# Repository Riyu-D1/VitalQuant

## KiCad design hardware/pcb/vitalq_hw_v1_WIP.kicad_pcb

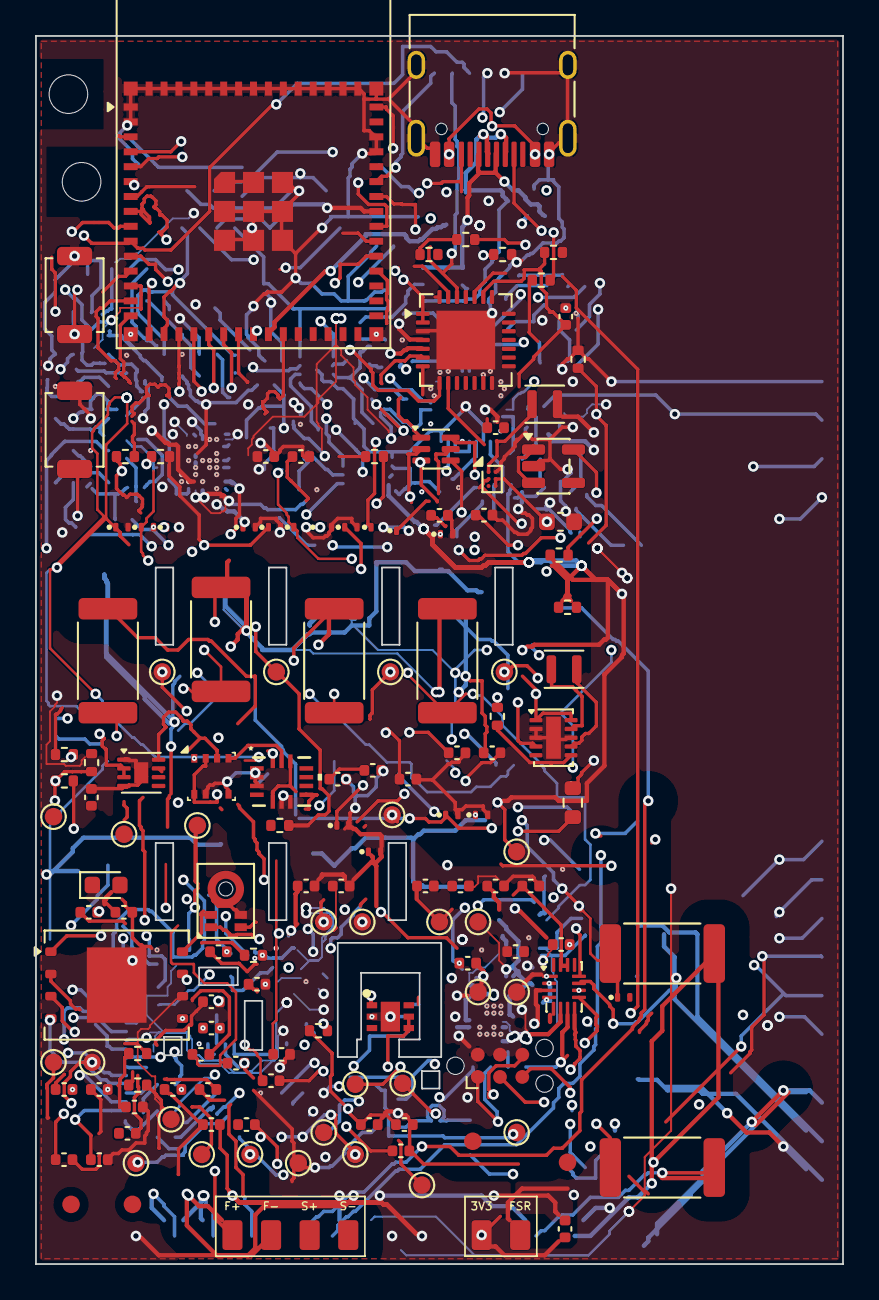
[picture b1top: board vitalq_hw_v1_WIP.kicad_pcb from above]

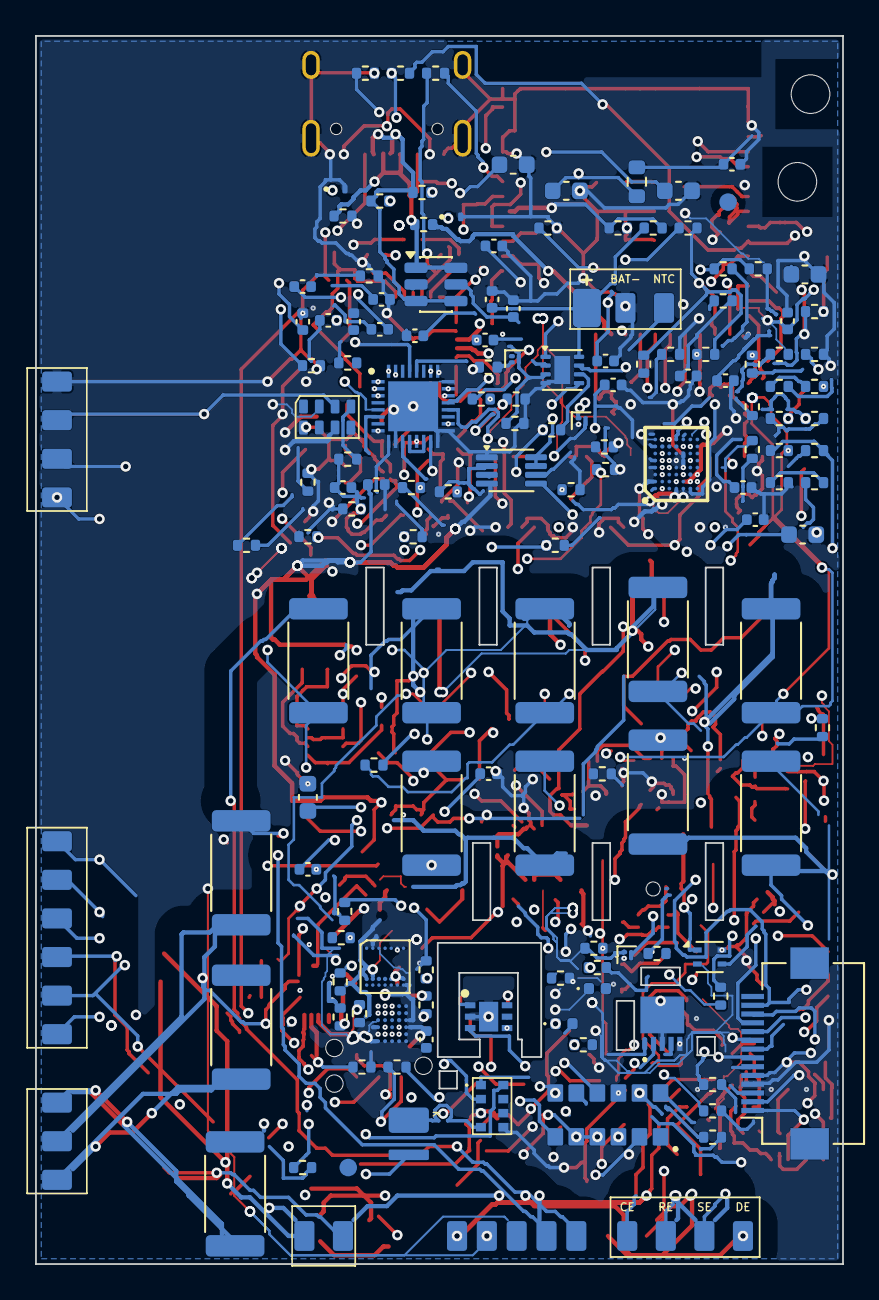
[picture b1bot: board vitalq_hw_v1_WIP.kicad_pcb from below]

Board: 6 copper layers, 46.0 x 70.0 mm, 292 parts (148 on the bottom side), 190 nets.

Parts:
C1, C47: 4.7u; C_0603_1608Metric
C2, C9, C20: 4.7u; C_0402_1005Metric
C3, C4, C6, C11, C14, C16, C19, C26, C32, C33, C42, C43, C64, C66, C80, C82, C83, C84: 1u; C_0402_1005Metric
C7, C45: 22u; C_0603_1608Metric
C8, C13, C15, C18, C24, C25, C27, C28, C29, C36, C37, C38, C39, C40, C41, C50, C51, C56, C57, C58, C59, C60, C61, C62, C63, C76, C77, C78, C79, C81: 100n; C_0402_1005Metric
C10: 1u; C_0603_1608Metric
C21, C22, C23, C55, C68, C69, C70: 470n; C_0402_1005Metric
C30: 10u; C_0402_1005Metric
C34: 47n; C_0402_1005Metric
C35: 4.7n; C_0402_1005Metric
C44: 10u; C_0603_1608Metric
C46: 2.2u; C_0402_1005Metric
C48, C49, C52, C53: 2.2n; C_0402_1005Metric
C54, C67: 15n; C_0402_1005Metric
C65: 1.5n; C_0402_1005Metric
C85: 47u; C_0603_1608Metric
D1, D2, D3, D4, D5, D6, D7, D8, D9, D21, D22, D23, D24, D26, D27, D28, D29, D30: TPD1E10B06; TPD1E10B06_DPY
D10: NF2W757G-F1; NF2W757G
D11: SFH4053; LED_0402_1005Metric
D12: SFH 4735 730nm; LED_0402_1005Metric
D25: KT-0603G; LED_0603_1608Metric
FID1, FID2, FID3, FID4, FID5, FID6: FID; Fiducial_1mm
H1, H2: M2; MountingHole_2.2mm_M2
J1: USB-C; USB_C_Receptacle_HRO_TYPE-C-31-M-12
J2: LiPo pads; Pads_LiPo
J3: FSR pads; Pads_FSR
J5: ECG pads; Pads_ECG
J6: EDA pads; Pads_EDA
J7: Chest bioZ; Pads_BIOZ
J8: TC2030; Tag-Connect_TC2030-IDC-NL_2x03_P1.27mm_Vertical
J9: I2C tail pads; Pads_1x04
J10: Optical tail pads; Pads_1x06
J11: Sweat site; Pads_1x03
J12: FH12-14S; Hirose_FH12-14S-0.5SH_1x14-1MP_P0.50mm_Horizontal
J13: MX ECG pads; Pads_1x02
L1: 0.47u; L_DFE201612E
L2: 1.0u; L_DFE201612E
Q1, Q2, Q4: CSD13380F3T; Texas_PicoStar_DFN-3_0.69x0.60mm
Q3: BC847BS,115; SOT-363_SC-70-6
R1, R2: 5.1k; R_0402_1005Metric
R3: 1.5k; R_0402_1005Metric
R5, R6, R7, R8, R9, R11, R14, R49, R52, R53, R60, R61, R65, R67, R68, R69, R70, R71, R74, R98, R100, R101, R112, R113, R115, R116, R117: 10k; R_0402_1005Metric
R10, R13, R39, R40, R41, R42, R62, R72, R73, R84, R85, R86, R87, R88: 1k; R_0402_1005Metric
R12: 10; R_0402_1005Metric
R15, R16, R17: 1M; R_0402_1005Metric
R18, R51: 200k; R_0402_1005Metric
R19, R20, R21, R22: 4.7k; R_0402_1005Metric
R23: 560k; R_0402_1005Metric
R24, R25, R44, R46, R48, R50, R59, R99, R107, R108, R110: 100k; R_0402_1005Metric
R26, R27, R28, R29: 10M; R_0402_1005Metric
R30, R31: 40.2k; R_0402_1005Metric
R32, R33, R34, R35, R36, R76, R77, R78, R79, R80, R81, R82, R83: 51k; R_2512_6332Metric
R43, R45: 5.11M; R_0402_1005Metric
R47, R109: 100; R_0402_1005Metric
R63: 22.1k; R_0402_1005Metric
R64: 47.5k; R_0402_1005Metric
R66: 301k; R_0402_1005Metric
R75: 27.0k; R_0402_1005Metric
R89, R90, R91, R92, R95, R96, R97, R102, R103, R104, R105, R106, R114: 0; R_0402_1005Metric
R93, R94: 0; R_0603_1608Metric
R118, R119, R120, R121, R122: 0; R_2512_6332Metric
SW1, SW2: TS-1088; SW_SPST_TS-1088-xR020
TP1: VBUS; TestPoint_Pad_D1.0mm
TP2: VBAT; TestPoint_Pad_D1.0mm
TP3: +3V3; TestPoint_Pad_D1.0mm
TP4: +1V8; TestPoint_Pad_D1.0mm
TP5: TX_5V; TestPoint_Pad_D1.0mm
TP6: VDD_CP2102; TestPoint_Pad_D1.0mm
TP7, TP8: GND; TestPoint_Pad_D1.0mm
TP9: ESP_EN; TestPoint_Pad_D1.0mm
TP10: ESP_IO0; TestPoint_Pad_D1.0mm
TP11: ESP_TX; TestPoint_Pad_D1.0mm
TP12: ESP_RX; TestPoint_Pad_D1.0mm
TP13: I2C_SDA; TestPoint_Pad_D1.0mm
TP14: I2C_SCL; TestPoint_Pad_D1.0mm
TP15: I2C_SDA_1V8; TestPoint_Pad_D1.0mm
TP16: I2C_SCL_1V8; TestPoint_Pad_D1.0mm
TP17: SPI_SCK; TestPoint_Pad_D1.0mm
TP18: SPI_MOSI; TestPoint_Pad_D1.0mm
TP19: SPI_MISO; TestPoint_Pad_D1.0mm
TP20: CS_ADS1292; TestPoint_Pad_D1.0mm
TP21: CS_AFE4900; TestPoint_Pad_D1.0mm
TP22: CS_AD5940; TestPoint_Pad_D1.0mm
TP23: CS_FLASH; TestPoint_Pad_D1.0mm
TP24: ADS1292_DRDY; TestPoint_Pad_D1.0mm
TP25: AFE4900_ADC_RDY; TestPoint_Pad_D1.0mm
TP26: EXP_INT; TestPoint_Pad_D1.0mm
TP27: CHG_STAT; TestPoint_Pad_D1.0mm
TP28: RTC_INT; TestPoint_Pad_D1.0mm
U1: ESP32-S3-MINI-1-N4R2; ESP32_S3_MINI_1
U2: BQ25170DSGR; Texas_DSG0008A_WSON-8-1EP_2x2mm_P0.5mm_EP0.9x1.6mm
U3: TPS63802DLAR; WSON-10-1EP_2x3mm_P0.5mm_EP0.84x2.4mm
U4: TPS7A2018PDBVR; SOT-23-5
U5: CP2102N-A02-GQFN28R; QFN-28-1EP_5x5mm_P0.5mm_EP3.35x3.35mm
U6: AFE4900YZR; BGA30N40P5X6_260X210X50
U7: AD5940BCBZ-RL7; BGA56C40P8X7_416X356X55
U8: ADS1292RIRSMT; QFN40P400X400X100-33N-D
U9: PCA9306DCUR; VSSOP-8_2.3x2mm_P0.5mm
U10: AS7341-DLGM; AS7341DLGT
U11, U20: TMP117AIDRVR; TMP117_DRV_NOPASTE
U12: MLX90632SLD-DCB-100-SP; MLX90632SLDDCB100SP
U13: BME280; Bosch_LGA-8_2.5x2.5mm_P0.65mm_ClockwisePinNumbering
U14: LSM6DSV80XTR; QFN_LSM6DSV80XTR_STM
U15: TPS61240YFFR; TPS61240_YFF
U16: SFH 7072; SFH7072
U17: MAX17048G+T10; TDFN-8-1EP_2x2mm_P0.5mm_EP0.8x1.2mm
U18: W25Q512JVEIQ; W25Q512_WSON8
U19: TCA6408ARSVR; TCA6408A_RSV
U21: USBLC6-2SC6; SOT-23-6
U22: MAX86178ENJ+; MAX86178_WLP49
U23: SHT45-AD1B; SHT45_DFN4
U24: RV-3028-C7; RV3028C7
U25: IM69D130

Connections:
+1V8: C36.1, R21.1, R22.1, R66.1, R97.2, TP4.1, U9.2, U10.1
+1V8_LDO: C6.1, R97.1, U4.5
+3V3: C4.1, C37.1, C38.1, C39.1, C40.1, C41.1, C45.1, C59.1, C60.1, C61.1, C76.1, C77.1, C78.1, C81.1, C84.1, D10.1, J3.1, J8.1, J9.1, J12.1, R5.1, R6.1, R7.1, R18.1, R19.1, R20.1, R23.1, R47.1, R49.1, R52.1, R53.1, R60.1, R65.1, R74.1, R94.1, R95.1, R98.1, R99.1, R109.1, R112.1, R113.1, R117.1, TP3.1, U3.6, U4.1, U4.3, U11.5, U12.2, U13.2, U13.6, U13.8, U14.5, U14.8, U14.12, U18.3, U18.7, U18.8, U19.14, U19.15, U20.4, U20.5, U22.F2, U23.3, U24.7, U25.2
+3V3_ANA: C11.1, C13.1, C16.1, C18.1, C28.1, C29.1, C43.1, C79.1, C80.1, R12.1, R15.1, R26.1, R28.1, R95.2, R116.1, U6.A4, U6.C1, U6.C4, U7.A4, U7.F2, U7.F3, U8.12, U8.14, U8.23, U22.F1
+3V3_ESP: C7.1, C8.1, R94.2, U1.3
AD5940_GPIO0: U1.18, U7.F5
AD5940_RESET: R11.1, U7.F1, U19.4
ADS1292_DRDY: R99.2, TP24.1, U1.6, U8.22
ADS1292_PWDN: R14.1, U8.15, U19.3
ADS_GPIO1: R100.1, U8.26
ADS_GPIO2: R101.1, U8.25
AFE4900_ADC_RDY: TP25.1, U1.25, U6.F4
AFE4900_RESETZ: R9.1, U6.E1, U19.2
AFE_BG: C15.1, U6.D2
AFE_CLK: R10.1, U6.F1
AFE_INM: C57.2, R45.2, U6.A1
AFE_INP: C56.2, R43.2, U6.B1
AFE_N_AC: D5.1, R36.2, R46.1
AFE_N_PAD: J5.5, R36.1
AFE_N_SER: C57.1, R46.2
AFE_P_AC: D4.1, R35.2, R44.1
AFE_P_PAD: J5.4, R35.1
AFE_P_SER: C56.1, R44.2
AIN4_LPF0: C26.1, U7.B4
AVDD_REG: C42.1, U7.D8
BIOZ_FN: C68.2, U7.D2
BIOZ_FN_PAD: J7.2, R81.1
BIOZ_FP: R84.2, U7.B3
BIOZ_FP_PAD: J7.1, R80.1
BIOZ_SN: C70.2, U7.A3
BIOZ_SN_PAD: J7.4, R83.1
BIOZ_SP: C69.2, U7.B5
BIOZ_SP_PAD: J7.3, R82.1
CE0: R39.2, U7.A7
CE_ISO: C54.2, D6.1, R39.1
CE_SURGE: C54.1, R76.2
CHG_DIS: Q2.1, R59.1, U19.10
CHG_ISET: R3.1, U2.2
CHG_PG: R60.2, U1.11, U2.6
CHG_STAT: R49.2, TP27.1, U2.5, U19.8
CHG_VSET: R75.1, U2.7
CP_DTR: Q3.4, R70.1, U5.28
CP_RST: R62.2, U5.9
CP_RTS: Q3.1, R71.1, U5.24
CP_RX: R72.2, U5.25
CP_TX: R73.1, U5.26
CP_VBUS: R63.2, R64.1, U5.8
CS_AD5940: R7.2, TP22.1, U1.19, U7.F7
CS_ADS1292: R98.2, TP20.1, U1.14, U8.18
CS_AFE4900: R116.2, TP21.1, U1.22, U6.E3
CS_FLASH: R52.2, TP23.1, U1.20, U18.1
CS_MAX86178: R117.2, U1.34, U22.G4
DE0: R42.2, U7.B6
DE_SURGE: D9.1, R42.1, R79.2
DVDD_REG: C23.1, U7.G3
ECG1_PAD: J5.1, R32.1
ECG2_PAD: J5.2, R33.1
ECG_N: C51.1, C53.1, D2.1, R31.2, R33.2, U8.5
ECG_P: C50.1, C52.1, D1.1, R30.2, R32.2, U8.6
EDA_CE_PAD: J6.1, R76.1
EDA_DE_PAD: J6.4, R79.1
EDA_RE_PAD: J6.2, R78.1
EDA_SE_PAD: J6.3, R77.1
ESP_EN: C64.1, J8.5, Q3.6, R5.2, SW1.1, TP9.1, U1.45, U19.1
ESP_IO0: J8.6, Q3.3, R6.2, SW2.1, TP10.1, U1.4
ESP_RX: J8.4, R73.2, TP12.1, U1.40
ESP_TX: J8.3, R72.1, TP11.1, U1.39
EXP_INT: R53.2, TP26.1, U1.7, U19.11
FB_3V3: R23.2, R24.1, U3.4
FN_ISO: C68.1, D22.1, R85.2
FN_SURGE: R81.2, R85.1
FP_ISO: C67.2, D21.1, R84.1
FP_SURGE: C67.1, R80.2
FSR_ADC: J3.2, R8.1, U1.5
GAUGE_ALRT: R74.2, U1.10, U17.5
GND: C1.2, C2.2, C3.2, C4.2, C6.2, C7.2, C8.2, C9.2, C10.2, C11.2, C13.2, C14.2, C15.2, C16.2, C18.2, C19.2, C20.2, C21.2, C22.2, C23.2, C24.2, C25.2, C26.2, C28.2, C29.2, C30.2, C32.2, C33.2, C36.2, C37.2, C38.2, C39.2, C40.2, C41.2, C42.2, C43.2, C44.2, C45.2, C46.2, C47.2, C48.2, C49.2, C52.2, C53.2, C58.2, C59.2, C60.2, C61.2, C62.2, C63.2, C64.2, C66.2, C76.2, C77.2, C78.2, C79.2, C80.2, C81.2, C82.2, C83.2, C84.2, C85.2, D1.2, D2.2, D3.2, D4.2, D5.2, D6.2, D7.2, D8.2, D9.2, D21.2, D22.2, D23.2, D24.2, D25.2, D26.2, D27.2, D28.2, D29.2, D30.2, J1.A1, J1.A12, J1.B1, J1.B12, J1.SH, J2.2, J8.2, J9.4, J12.4, Q1.2, Q2.2, Q4.2, R1.2, R2.2, R3.2, R8.2, R9.2, R10.2, R11.2, R14.2, R16.2, R24.2, R25.2, R27.2, R29.2, R48.2, R51.2, R59.2, R61.2, R64.2, R66.2, R75.2, R100.2, R101.2, R108.2, R110.2, R115.2, SW1.2, SW2.2, TP7.1, TP8.1, U1.1, U1.2, U1.42, U1.43, U1.46, U1.47, U1.48, U1.49, U1.50, U1.51, U1.52, U1.53, U1.54, U1.55, U1.56, U1.57, U1.58, U1.59, U1.60, U1.61, U1.62, U1.63, U1.64, U1.65, U2.4, U2.9, U3.2, U3.3, U3.8, U3.11, U4.2, U5.3, U5.29, U6.B4, U6.D1, U6.D5, U7.C4, U7.D5, U7.E3, U7.E4, U7.E5, U7.E6, U8.10, U8.13, U8.16, U8.17, U8.24, U8.33, U9.1, U10.3, U10.5, U11.2, U11.4, U11.7, U12.3, U12.5, U12.6, U13.1, U13.5, U13.7, U14.1, U14.2, U14.3, U14.6, U14.7, U15.A2, U17.1, U17.4, U17.6, U17.9, U18.4, U18.9, U19.6, U19.16, U20.2, U20.7, U21.2, U22.F5, U22.F6, U22.F7, U23.4, U24.5, U24.8, U25.4, U25.5
I2C_SCL: J9.3, J12.3, R20.2, TP14.1, U1.13, U9.6, U11.1, U13.4, U14.13, U17.7, U19.12, U20.1, U23.2, U24.3
I2C_SCL_1V8: R22.2, TP16.1, U9.3, U10.2, U12.4
I2C_SDA: J9.2, J12.2, R19.2, TP13.1, U1.12, U9.5, U11.6, U13.3, U14.14, U17.8, U19.13, U20.6, U23.1, U24.4
I2C_SDA_1V8: R21.2, TP15.1, U9.4, U10.8, U12.1
IN1N: C49.1, R28.2, R29.1, R68.2, U8.3
IN1N_AC: C51.2, R68.1
IN1P: C48.1, R26.2, R27.1, R67.2, U8.4
IN1P_AC: C50.2, R67.1
IOVDD: C19.1, R12.2, U7.G2
IR_AN: D11.1, R47.2
IR_GATE: Q1.1, R48.1, U19.7
IR_K: D11.2, Q1.3
J11_CE: J11.3, R122.1
J11_RE: J11.2, R121.1
J11_WE: J11.1, R120.1
J13_INM: J13.2, R119.1
J13_INP: J13.1, R118.1
LDR: D10.2, U10.4
LED1_K: J10.1, J12.5, U22.A3
LED2_K: J10.2, J12.6, U22.A4
LED3_K: J10.3, J12.7, U22.A5
LED_A: D25.1, R88.2
LED_AN: J10.4, J12.8, R114.2
LSM6_INT1: U1.8, U14.4
MAX86178_INT: R113.2, U1.35, U22.G3
MIC_CLK: U1.36, U25.3
MIC_DAT: U1.37, U25.1
MISO_AD: R91.1, U7.E8
MISO_ADS: R89.1, U8.21
MISO_AFE: R90.1, U6.E2
MISO_FL: R92.1, U18.2
MISO_MX: R106.1, U22.G5
MX_ECG_INM: D30.1, R119.2, U22.A7
MX_ECG_INP: D29.1, R118.2, U22.A6
MX_VREF: C83.1, U22.F4
NIR730_GATE: Q4.1, R110.1, U7.E1
NIR_AN: D12.1, R109.2
NIR_K: D12.2, Q4.3
PD2_INM: U6.B3, U16.10
PD2_INP: U6.B2, U16.3
PD_A: J10.6, J12.10, U22.A1
PD_INM: U6.A3, U16.2
PD_INP: U6.A2, U16.1
PD_K: J10.5, J12.9, U22.A2
PGA1N: C34.1, U8.1
PGA1P: C34.2, U8.2
PGA2N: C35.1, U8.7
PGA2P: C35.2, U8.8
Q3_B1: Q3.2, R70.2
Q3_B2: Q3.5, R71.2
RC0_0: C27.1, U7.C8
RC0_1: C27.2, U7.B8
RCAL0: R13.1, U7.C1
RCAL1: R13.2, U7.B1
RE0: R41.2, U7.A8
RESP_MODN: R31.1, U8.32
RESP_MODP: R30.1, U8.31
RE_SURGE: D8.1, R41.1, R78.2
RLDINV: C65.2, R17.2, U8.28
RLDOUT: C65.1, R17.1, R43.1, R45.1, R69.2, U8.30
RLDREF: C66.1, R15.2, R16.1, U8.29
RLD_CLAMP: D3.1, R34.2, R69.1
RLD_PAD: J5.3, R34.1
RTC_INT: R112.2, TP28.1, U24.2
RTC_VBK: R115.1, U24.6
SE0: C55.2, U7.A6
SE_ISO: C55.1, D7.1, R40.2
SE_SURGE: R40.1, R77.2
SN_ISO: C70.1, D24.1, R87.2
SN_SURGE: R83.2, R87.1
SPARE_IN: R107.2, R108.1, U1.38
SPI_MISO: R89.2, R90.2, R91.2, R92.2, R106.2, TP19.1, U1.17
SPI_MOSI: TP18.1, U1.15, U6.F2, U7.E7, U8.19, U18.5, U22.G6
SPI_SCK: TP17.1, U1.16, U6.F3, U7.F8, U8.20, U18.6, U22.G7
SP_ISO: C69.1, D23.1, R86.2
SP_SURGE: R82.2, R86.1
STATUS_LED: R88.1, U1.21
SWEAT_CE: D28.1, J12.13, R122.2, U7.A1
SWEAT_RE: D27.1, J12.12, R121.2, U7.A2
SWEAT_WE: D26.1, J12.11, R120.2, U7.C5
SW_L1: L1.1, U3.9
SW_L2: L1.2, U3.7
TMP117_ALERT: R65.2, U1.9, U11.3
TS: J2.3, Q2.3, R61.1, U2.3
TX1: U6.D4, U16.6
TX2: U6.E5, U16.12
TX3: U6.E4, U16.8
TX4: U6.C5, U16.9
TX5_EN: R25.1, U15.C1, U19.5
TX_5V: C14.1, R96.2, R114.1, TP5.1, U6.F5, U16.4, U16.5, U16.7, U16.11
TX_5V_RAW: C47.1, R96.1, U15.B2, U15.C2
TX_SW: L2.2, U15.B1
USB_CC1: J1.A5, R1.1
USB_CC2: J1.B5, R2.1
USB_DM: J1.A7, J1.B7, R103.1, R105.1, U21.3, U21.4
USB_DM_CP: R105.2, U5.5
USB_DM_S3: R103.2, U1.23
USB_DP: J1.A6, J1.B6, R102.1, R104.1, U21.1, U21.6
USB_DP_CP: R104.2, U5.4
USB_DP_S3: R102.2, U1.24
VBAT: C2.1, C3.1, C58.1, C82.1, C85.1, J2.1, R93.1, R107.1, TP2.1, U2.8, U17.2, U17.3, U22.F3
VBAT_SYS: C44.1, C46.1, L2.1, R93.2, U3.1, U3.10, U15.A1
VBIAS0: C25.1, U7.C7
VBIAS_CAP: C22.1, U7.D1
VBUS: C1.1, C10.1, C63.1, J1.A4, J1.A9, J1.B4, J1.B9, R50.1, R63.1, TP1.1, U2.1, U5.7, U21.5
VBUS_DET: R50.2, R51.1, U19.9
VCAP1: C32.1, U8.11
VCAP2: C33.1, U8.27
VDD_CP2102: C9.1, C62.1, R62.1, TP6.1, U5.1, U5.2, U5.6, U5.23, U5.27
VREF2: R18.2, U9.7, U9.8
VREFP: C30.1, U8.9
VREF_1V82: C20.1, U7.A5
VREF_2V5: C21.1, U7.D7
VZERO0: C24.1, U7.B7

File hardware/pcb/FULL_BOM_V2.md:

# hw_v2 — Full Board BOM (every component)

292 placed parts on `devin/hw-v2-pcb`. Per single board.
"DNP" = designed in but not populated at assembly.

## ICs & modules — 25

| Ref | Part (orderable MPN) | Package | LCSC | Notes |
|---|---|---|---|---|
| U1 | ESP32-S3-MINI-1-N4R2 | Module 15.4×20.5 | C3013941 | MCU, integrated antenna |
| U2 | BQ25170DSGR | WSON-8 | — | LiPo charger |
| U3 | TPS63802DLAR | WSON-10 | — | Buck-boost +3V3 |
| U4 | TPS7A2018PDBVR | SOT-23-5 | — | 1.8 V LDO |
| U5 | CP2102N-A02-GQFN28R | QFN-28 | — | USB-UART (strap option) |
| U6 | AFE4900YZR | BGA-30 | — | PPG/SpO2 AFE |
| U7 | AD5940BCBZ-RL7 | BGA-56 | C650308 | EDA/BioZ potentiostat |
| U8 | ADS1292RIRSMT | QFN-33 | C882777 | ECG AFE |
| U9 | PCA9306DCUR | VSSOP-8 | — | I2C level shifter |
| U10 | AS7341-DLGM | OLGA-8 | — | Spectral sensor |
| U11, U20 | TMP117AIDRVR | DRV-6 | — | Skin + ambient temp ×2 |
| U12 | MLX90632SLD-DCB-100-SP | SFN-5 | — | IR temperature |
| U13 | BME280 | LGA-8 | — | Ambient P/RH/T |
| U14 | LSM6DSV80XTR | LGA-14 | — | IMU |
| U15 | TPS61240YFFR | DSBGA-6 | — | TX_5V boost |
| U16 | SFH 7072 | Module | C2655172 | Optical emitter+PD |
| U17 | MAX17048G+T10 | TDFN-8 | C2682616 | Fuel gauge |
| U18 | W25Q512JVEIQ | WSON-8 | — | 512 Mbit flash |
| U19 | TCA6408ARSVR | UQFN-8 | C2649390 | GPIO expander |
| U21 | USBLC6-2SC6 | SOT-23-6 | C7519 | USB ESD array |
| U22 | MAX86178ENJ+ | WLP-49 | — | ECG/PPG/BioZ AFE (NDA part) |
| U23 | SHT45-AD1B(-R2) | DFN-4 | — | Humidity/temp |
| U24 | RV-3028-C7 | SON-8 | — | **DNP** RTC |
| U25 | IM69D130V01XTSA1 | LLGA-5 | — | **DNP** PDM mic |

## Optical emitters — 4

| Ref | Part | Pkg | Qty |
|---|---|---|---|
| D10 | NF2W757G-F1 white LED | NF2W757G | 1 |
| D11 | SFH 4053 IR emitter | 0402 | 1 |
| D12 | SFH 4735 730 nm NIR | 0402 | 1 |
| D25 | KT-0603G green status LED | 0603 | 1 (C12624) |

## ESD / protection — 19

| Part | Refs | Qty fitted | DNP |
|---|---|---|---|
| TPD1E10B06DPYR | D1–D9, D21–D24 | 13 | D26–D30 (5) |
| USBLC6-2SC6 | (listed above, U21) | — | — |

## Connectors / switches — 4 orderable

| Ref | Part | Qty | Status |
|---|---|---|---|
| J1 | TYPE-C-31-M-12 USB-C receptacle | 1 | Fitted |
| J12 | FH12-14S-0.5SH(55) FFC-14 | 1 | DNP |
| SW1, SW2 | TS-1088-AR02016 tactile | 2 | Fitted (C720477) |
| J2,J3,J5,J6,J7,J8,J9,J10,J11,J13 | Solder pads / TC2030 footprint | — | Board features, no orderable part |

## Magnetics — 2

| Ref | Part | Value |
|---|---|---|
| L1 | DFE201612E-R47M | 0.47 µH |
| L2 | DFE201612E-1R0M | 1.0 µH |

## Transistors — 4

| Ref | Part | LCSC |
|---|---|---|
| Q1, Q2, Q4 | CSD13380F3T N-FET PicoStar ×3 | C2871092 |
| Q3 | BC847BS,115 dual NPN SOT-363 | — |

## Capacitors — 72

| MPN | Value / Pkg | Qty fit | DNP | Refs |
|---|---|---|---|---|
| GRM155R71C104KA88 | 100 nF / 0402 | 28 | 2 | C8,C13,C15,C18,C24,C25,C27–C29,C36–C41,C50,C51,C56–C63,C76,C79,C81 (+C77,C78) |
| GRM155R61A105KE15 | 1 µF / 0402 | 18 | 0 | C3,C4,C6,C11,C14,C16,C19,C26,C32,C33,C42,C43,C64,C66,C80,C82,C83,C84 |
| GRM155R61A474KE15 | 470 nF / 0402 | 7 | 0 | C21–C23,C55,C68–C70 |
| GRM1555C1H222JA01 | 2.2 nF / 0402 | 4 | 0 | C48,C49,C52,C53 |
| GRM155R60J475ME87 | 4.7 µF / 0402 | 3 | 0 | C2,C9,C20 |
| GRM155R71H153KA12 | 15 nF / 0402 | 2 | 0 | C54,C67 |
| CL10A476MQ8NRNC | 47 µF / 0603 | 1 | 0 | C85 (C19702) |
| CL10A226MQ8NRNC | 22 µF / 0603 | 1 | 0 | C7 (C59461) |
| GRM188R61A226ME15 | 22 µF / 0603 | 1 | 0 | C45 |
| CL10A475KA8NQNC | 4.7 µF / 0603 | 1 | 0 | C1 (C69335) |
| GRM188R61A475KE15 | 4.7 µF / 0603 | 1 | 0 | C47 |
| GRM188R61A106ME69 | 10 µF / 0603 | 1 | 0 | C44 |
| GRM155R60J106ME05 | 10 µF / 0402 | 1 | 0 | C30 |
| CL10A105KA8NNNC | 1 µF / 0603 | 1 | 0 | C10 |
| GRM155R60J225ME15 | 2.2 µF / 0402 | 1 | 0 | C46 |
| GRM155R71H473KA88 | 47 nF / 0402 | 1 | 0 | C34 |
| GRM1555C1H472JA01 | 4.7 nF / 0402 | 1 | 0 | C35 |
| GRM1555C1H152JA01 | 1.5 nF / 0402 | 1 | 0 | C65 |

## Resistors — 96

| MPN | Value / Pkg | Qty fit | DNP | Refs |
|---|---|---|---|---|
| RC0402FR-0710KL | 10 kΩ / 0402 | 24 | 2 | R5–R9,R11,R14,R49,R52,R53,R60,R65,R67–R71,R74,R98,R100,R101,R113,R116,R117 (+R112,R115) C25744 |
| RC0402FR-071KL | 1 kΩ / 0402 | 14 | 0 | R10,R13,R39–R42,R62,R72,R73,R84–R88 (C11702) |
| DPCR2512-51KJT18 | 51 kΩ / 2512 | 13 | 0 | R32–R36, R76–R83 (HV ladder) |
| 0402WGF0000TCE | 0 Ω / 0402 | 11 | 2 | R89–R92,R95–R97,R102,R103,R106,R114 (+R104,R105) C17168 |
| RC0402FR-07100KL | 100 kΩ / 0402 | 9 | 2 | R24,R25,R44,R46,R48,R50,R59,R99,R110 (+R107,R108) C25741 |
| 25121WJ0000T4E | 0 Ω / 2512 | 5 | 0 | R118–R122 (HV cut-points) C2908946 |
| RC0402FR-074K7L | 4.7 kΩ / 0402 | 4 | 0 | R19–R22 |
| 0402WGF1005TCE | 10 MΩ / 0402 | 4 | 0 | R26–R29 (C26082) |
| RC0402FR-071ML | 1 MΩ / 0402 | 3 | 0 | R15–R17 |
| RC0402FR-075K1L | 5.1 kΩ / 0402 | 2 | 0 | R1,R2 |
| RC0402FR-0740K2L | 40.2 kΩ / 0402 | 2 | 0 | R30,R31 |
| RC0402FR-075M11L | 5.11 MΩ / 0402 | 2 | 0 | R43,R45 |
| RC0402FR-07100RL | 100 Ω / 0402 | 2 | 0 | R47,R109 |
| RC0402FR-07200KL | 200 kΩ / 0402 | 2 | 0 | R18,R51 |
| 0603WAF0000T5E | 0 Ω / 0603 | 2 | 0 | R93,R94 (C21189) |
| RC0402FR-0710RL | 10 Ω / 0402 | 1 | 0 | R12 |
| 0402WGF1501TCE | 1.5 kΩ / 0402 | 1 | 0 | R3 (C25867) |
| RC0402FR-07560KL | 560 kΩ / 0402 | 1 | 0 | R23 |
| NCU15XH103F6SRC | 10 kΩ NTC / 0402 | 0 | 1 | R61 (DNP — cell NTC option) |
| RC0402FR-0722K1L | 22.1 kΩ / 0402 | 1 | 0 | R63 |
| RC0402FR-0747K5L | 47.5 kΩ / 0402 | 1 | 0 | R64 |
| RC0402FR-07301KL | 301 kΩ / 0402 | 1 | 0 | R66 |
| RC0402FR-0727KL | 27 kΩ / 0402 | 1 | 0 | R75 |

## Board features (no part to buy)

- TP1–TP28 test-point pads (28)
- FID1–FID6 fiducials (6)
- H1, H2 M2 mounting holes
- J2/J3/J5/J6/J7/J9/J10/J11/J13 solder-pad fields, J8 TC2030 pads

## Distinct orderable line items: 57
## Totals per board: 281 fitted + 11 DNP parts

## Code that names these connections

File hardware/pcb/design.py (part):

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#     the J13 ECG pad pair (DNP). J12 is 14-pos, not the spec's 12: the
#     three tails carry 13 nets, so a 14-pos FFC (FH12-14S-0.5SH) is the smallest that fits.
#   * SHT45 U23 on I2C 0x44 (skin side); RV-3028-C7 RTC U24 at 0x52;
#     IM69D130 PDM mic U25 on MIC_CLK/MIC_DAT (GPIO40/41); D12 730 nm LED
#     + Q4 CSD13380F3T gated by AD5940 GPIO2 (ball E1, net NIR730_GATE).
#   * Strict superset: no hw_v1 part, net, TVS, or test point was removed.
#     New symbols are drawn in-file by hw_v2_lib() so lib/*.kicad_sym and the
#     library build script stay untouched.
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        "15": "SPI_MOSI",  # IO11
        "16": "SPI_SCK",  # IO12
        "17": "SPI_MISO",  # IO13
        "18": "AD5940_GPIO0",  # IO14
        "19": "CS_AD5940",  # IO15
        "20": "CS_FLASH",  # IO16, W25Q512
        "21": "STATUS_LED",  # IO17 -> R88 -> D25 -> GND
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        "36": "MIC_CLK",  # IO40 — IM69D130 PDM clock (DNP)
        "37": "MIC_DAT",  # IO41 — IM69D130 PDM data (DNP)
        "38": "SPARE_IN",    # IO42 — MTMS, digital-only (no SAR ADC on S3); spare input
        "39": "ESP_TX",  # TXD0 = GPIO43 -> R72 -> CP2102 RXD
        "40": "ESP_RX",  # RXD0 = GPIO44 <- R73 <- CP2102 TXD
        "41": "NC",  # IO45 — strap pin, left unstrapped (no load)
        "44": "NC",  # IO46 — strap pin, left unstrapped (no load)
    }
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        "B1": "AFE_INP",
        "A2": "PD_INP",
        "A3": "PD_INM",
        "B2": "PD2_INP",
        "B3": "PD2_INM",
        "B5": "NC",
        "A5": "NC",
        "C2": "NC",  # RLD_OUT stays off
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    opt = d.part(sh, "SFH7072", "U16", "SFH 7072", FP_SFH, 70, 90, labels="ic")
    d.stub_net(sh, opt, "1", "PD_INP", 7.62)
    d.stub_net(sh, opt, "2", "PD_INM", 7.62)
    d.stub_net(sh, opt, "3", "PD2_INP", 7.62)
    d.stub_net(sh, opt, "10", "PD2_INM", 7.62)
    d.join_row(sh, opt, ["4", "5", "7", "11"], "TX_5V", 7.62)
    d.stub_net(sh, opt, "6", "TX1", 7.62)
    d.stub_net(sh, opt, "12", "TX2", 7.62)
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        "D6": "NC",
        "D7": "VREF_2V5",
        "D8": "AVDD_REG",
        "E1": "NIR730_GATE",  # GPIO2 — hw_v2: gates Q4, the 730 nm LED
        "E2": "NC",
        "E3": "GND",
        "E4": "GND",
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        "F2": "+3V3_ANA",
        "F3": "+3V3_ANA",
        "F4": "NC",
        "F5": "AD5940_GPIO0",
        "F6": "NC",
        "F7": "CS_AD5940",
        "F8": "SPI_SCK",
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    d.flag_net(sh, "IOVDD", 175, 203)

    sh.text("C16 AVDD, C18 DVDD, C42 AVDD_REG, C19 IOVDD after R12, C20-C26 are the reference and bias caps.", 16, 236, 1.35)
    sh.text("R13 is RCAL. C27 sits between RC0_0 and RC0_1. XTAL pins are open: the internal oscillator is used.", 16, 242, 1.35)
    # Surge resistor on the pad, then the AN-1557 network. C54 is behind R76.
    d.hpart(sh, "R", "R76", "51k", FP_HV, 200, 210, "EDA_CE_PAD", "CE_SURGE")
    d.hpart(sh, "C", "C54", "15n", FP_C, 255, 210, "CE_SURGE", "CE_ISO")
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    d.vpart(sh, "D_TVS_2", "D8", "TPD1E10B06", FP_TVS, 400, 202, "RE_SURGE", "GND")
    d.vpart(sh, "D_TVS_2", "D9", "TPD1E10B06", FP_TVS, 400, 228, "DE_SURGE", "GND")
    sh.text("R76-R79 are the pad-side 51k DPCR. C54 sits behind R76. R39 stays the 1k RLIMIT. No gas tube.", 16, 268, 1.3)
    sh.text("hw_v2: AIN6/AFE3/AFE4 feed J11 (RESEARCH-GRADE sweat site) and GPIO2 is NIR730_GATE. Other GPIO balls stay open.", 16, 274, 1.3)
    # Chest 4-wire. Same pad-side order as EDA. Force uses the Fig 54 15 nF and 1 kΩ.
    # The other three lines use 470 nF. 26 mm keeps a TPD GND stub off the next label.
    d.hpart(sh, "R", "R80", "51k", FP_HV, 230, 114, "BIOZ_FP_PAD", "FP_SURGE")
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        "20": "SPI_SCK",
        "21": "MISO_ADS",
        "22": "ADS1292_DRDY",
        "25": "ADS_GPIO2",
        "26": "ADS_GPIO1",
        "33": "GND",  # exposed pad, must be AVSS
    }
    d.side_map(sh, u, side, 8.89)
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    d.hpart(sh, "R", "R17", "1M", FP_R, 175, 240, "RLDOUT", "RLDINV")
    d.hpart(sh, "C", "C65", "1.5n", FP_C, 230, 200, "RLDOUT", "RLDINV")
    d.vpart(sh, "C", "C66", "1u", FP_C, 175, 155, "RLDREF", "GND")
    d.vpart(sh, "R", "R100", "10k", FP_R, 210, 155, "ADS_GPIO1", "GND")
    d.vpart(sh, "R", "R101", "10k", FP_R, 235, 155, "ADS_GPIO2", "GND")

    # Fig 68. Electrode node is ECG_P / ECG_N, after the series resistor.
    d.vpart(sh, "R", "R26", "10M", FP_R, 250, 185, "+3V3_ANA", "IN1P")
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    rtc = d.part(sh, "RV-3028-C7", "U24", "RV-3028-C7", FP_RTC, 360, 235, labels="ic")
    d.stub_net(sh, rtc, "3", "I2C_SCL", 7.62)
    d.stub_net(sh, rtc, "4", "I2C_SDA", 7.62)
    d.stub_net(sh, rtc, "2", "RTC_INT", 7.62)  # open-drain /INT — no host GPIO assigned
    d.stub_net(sh, rtc, "8", "GND", 7.62)      # EVI tied low
    d.join_row(sh, rtc, ["7"], "+3V3", 6.35)   # VDD
    d.join_row(sh, rtc, ["5"], "GND", 6.35)  # VSS
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
    # D12: 730 nm NIR LED for the AS7341 StO2 channel. Same switch pattern
    # as Q1/D11: 100R from +3V3, cathode to the CSD13380F3 drain. Gate is
    # AD5940 ball E1 (GPIO2) on net NIR730_GATE, pulled down by R110.
    d.vpart(sh, "R", "R109", "100", FP_R, 30, 245, "+3V3", "NIR_AN")
    d.vpart(sh, "LED_AK", "D12", "SFH 4735 730nm", FP_IR, 30, 270, "NIR_AN", "NIR_K")  # VERIFY: emitter choice
    q4 = d.part(sh, "CSD13380F3", "Q4", "CSD13380F3T", FP_FET, 185, 275, labels="ic")
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
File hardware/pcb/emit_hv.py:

#!/usr/bin/env python3
"""Emit the 16 HV/electrode nets via deterministic BFS flood routing.

Suppresses lane-squatter nets (obs.dead) so the reserved corridors are
usable; victims are re-routed afterwards by worker_route.py.
Round 0 emits at HW width; rounds 1-2 retry stragglers at 0.12mm.

usage: emit_hv.py <board> <pro_file>
"""
import sys
import time
import shutil
sys.path.insert(0, '.')
import pcbnew
import route_all as ra
import route_hv as rh
import route_hv_all as rha
from route_flood import pad_cells, bfs

IN = sys.argv[1]
PRO = sys.argv[2] if len(sys.argv) > 2 else IN.replace('.kicad_pcb', '.kicad_pro')

# nets whose lane-region copper was ripped / whose remaining copper must
# not block the corridors; all are re-routed afterwards.
DEAD = {
    '+1V8', '+3V3', '+3V3_ANA', 'AFE4900_ADC_RDY', 'AFE_CLK', 'AFE_N_AC',
    'AFE_P_AC', 'CE_SURGE', 'CHG_STAT', 'CS_AFE4900', 'CS_FLASH',
    'DE_SURGE', 'ECG_N', 'ECG_P', 'EXP_INT', 'FN_ISO', 'FN_SURGE',
    'FSR_ADC', 'GND', 'I2C_SDA', 'LED2_K', 'LED3_K', 'LED_A', 'MISO_AD',
    'MISO_FL', 'MX_ECG_INM', 'MX_ECG_INP', 'PD_A', 'PD_K', 'RE_SURGE',
    'RLDREF', 'RLD_CLAMP', 'RTC_INT', 'SE_SURGE', 'SWEAT_CE', 'SWEAT_RE',
    'VBUS',
    # second wave — non-HV nets whose vias/segs seal the corridor field
    'Q3_B1', 'CS_ADS1292', 'RC0_0', 'RC0_1', '+1V8_LDO', 'FP_ISO',
    'FN_ISO2', 'ESP_TX', 'ESP_RX', 'CP_RX', 'CP_TX', 'VBAT_SYS', 'VBAT',
    'FB_3V3', 'TX_SW', 'TX_5V', 'RX_5V', 'ADS_GPIO1', 'ADS_GPIO2',
    'AIN4_LPF0', 'AIN4_LPF1', 'LED1_K', 'LED4_K', 'FP_SURGE', 'SP_SURGE',
    'SN_SURGE', 'IN1P', 'IN1N', 'SPI_MISO', 'SPI_MOSI', 'SPI_SCK',
    'SCK_FL', 'MOSI_FL', 'CS_AD5940', 'Q3_B2', 'GAUGE_ALRT', 'AFE_INM',
    'AFE_INP', 'RLDOUT', 'MX_ADS_DRDY', 'I2C_SCL', 'CHG_PG', 'TS_EN',
    'BAT_NTC', 'MIC_B', 'MIC_A', 'HUM_SDA', 'HUM_SCL', 'TP_VBAT',
    'SW_CLK', 'SW_DIO', 'ESP_EN', 'ESP_IO0', 'U1_RX', 'U1_TX',
}

b = pcbnew.LoadBoard(IN)
assert ra.class_of(b, 'ECG1_PAD') == 'HV_ELECTRODE', 'netclasses unresolved!'
obs = ra.Obstacles(b)
guard = rh.SlotGuard(obs, b)
guard.wrap(obs)
rha.sibling_wrap(b, obs, guard)
obs.dead |= DEAD

todo = list(rha.PLANS)
passed = []
for rnd in range(3):
    still = []
    for net, (sref, sname), planf in todo:
        cls = ra.class_of(b, net)
        hw = rha.HW if rnd == 0 else 0.06
        _, (gref, gname) = planf()
        seed = pad_cells(b, sref, sname, net, cls, obs, hw)
        goals = pad_cells(b, gref, gname, net, cls, obs, hw)
        t0 = time.time()
        path, n = bfs(obs, seed, goals, net, cls, hw, cap=1500000)
        stat = 'UNREACHABLE'
        if path:
            sp = ra.simplify(path)
            pc = ra.path_clear(obs, sp, net, cls, hw)
            wv = rh.path_wall_violation(guard, sp, hw)
            if pc and not wv:
                ra.emit(b, obs, sp, net, hw * 2)
                stat = f'EMITTED {len(sp)}segs'
            else:
                stat = f'unsafe(c={pc},w={wv})'
        print(f'[r{rnd}] {net}: {stat} ({n}c,{time.time()-t0:.0f}s)',
              flush=True)
        pcbnew.SaveBoard(IN, b)
        dst = IN.replace('.kicad_pcb', '.kicad_pro')
        if dst != PRO:
            shutil.copy(PRO, dst)
        if stat.startswith('EMITTED'):
            passed.append(net)
        else:
            still.append((net, (sref, sname), planf))
    todo = still
    if not still:
        break
    print(f'== round {rnd} done, {len(still)} left ==', flush=True)
print(f'== FINISHED: {len(passed)} routed: {passed}', flush=True)
print(f'== open: {[n for n, _, _ in todo]}', flush=True)
